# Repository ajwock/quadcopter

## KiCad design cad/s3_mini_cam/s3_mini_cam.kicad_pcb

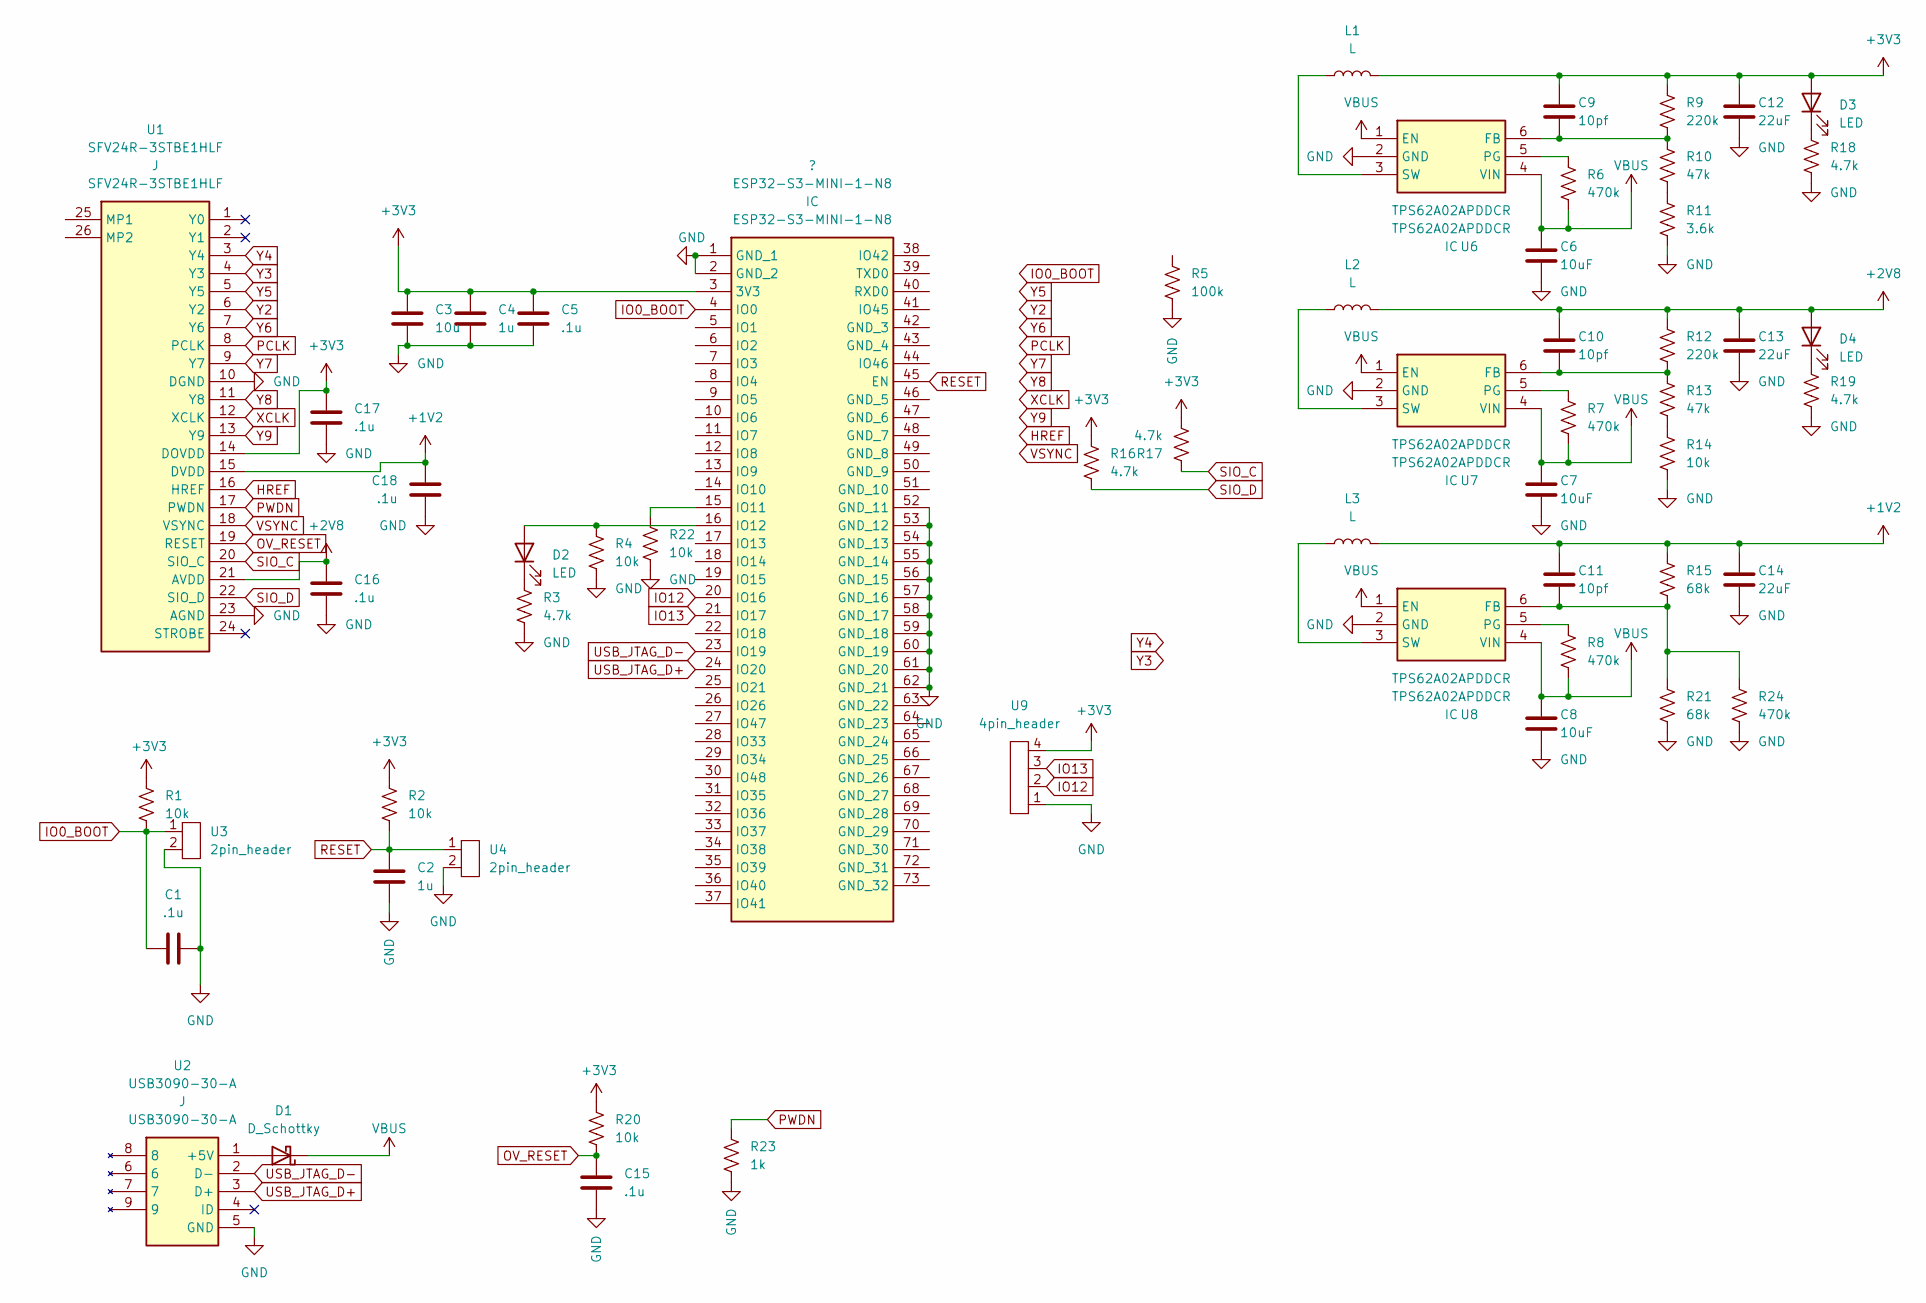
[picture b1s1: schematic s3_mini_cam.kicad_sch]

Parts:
C1, C5, C15, C16, C17, C18: .1u; C_0603_1608Metric
C2, C4: 1u; C_0603_1608Metric
C3: 10u; C_0603_1608Metric
C6, C7, C8: 10uF; 0603_cap
C9, C10, C11: 10pf; 0603_cap
C12, C13, C14: 22uF; 0603_cap
D1: D_Schottky; SM6F22AY
D2, D3, D4: LED; LED_0603_1608Metric
L1, L2, L3: L; L_0603_1608Metric
R1, R2, R20: 10k; R_0603_1608Metric
R3, R16, R17, R18, R19: 4.7k; 0603_resistor
R4, R14, R22: 10k; 0603_resistor
R5: 100k; 0603_resistor
R6, R7, R8, R24: 470k; 0603_resistor
R9, R12: 220k; 0603_resistor
R10, R13: 47k; 0603_resistor
R11: 3.6k; 0603_resistor
R15, R21: 68k; 0603_resistor
R23: 1k; R_0603_1608Metric
U1: SFV24R-3STBE1HLF; SFV24R3STBE1HLF; Mouser Part Number 649-SFV24R-3STBE1HLF
U2: USB3090-30-A; USB309030A; Mouser Part Number 640-USB3090-30-A
U3, U4: 2pin_header; 2-bb
U6, U7, U8: TPS62A02APDDCR; SOT95P280X110-6N; Mouser Part Number 595-TPS62A02APDDCR
U9: 4pin_header; 4-bb

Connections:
+1V2: C11.1, C14.1, C18.1, L3.2, R15.1, U1.15 (DVDD)
+2V8: C10.1, C13.1, C16.1, D4.2 (A), L2.2, R12.1, U1.21 (AVDD)
+3V3: C3.1, C4.1, C5.1, C9.1, C12.1, C17.1, D3.2 (A), L1.2, R1.1, R2.1, R9.1, R16.1, R17.2, R20.1, U1.14 (DOVDD), U9.4; also elsewhere on the board
GND: C1.1, C2.2, C3.2, C4.2, C5.2, C6.2, C7.2, C8.2, C12.2, C13.2, C14.2, C15.2, C16.2, C17.2, C18.2, R3.2, R4.2, R5.2, R11.2, R14.2, R18.2, R19.2, R21.2, R22.2, R23.2, R24.2, U1.10 (DGND), U1.23 (AGND), U2.5 (GND), U3.2, U4.2, U6.2 (GND), U7.2 (GND), U8.2 (GND), U9.1; also elsewhere on the board
HREF: U1.16 (HREF); also elsewhere on the board
IO0_BOOT: C1.2, R1.2, U3.1; also elsewhere on the board
IO12: U9.2; also elsewhere on the board
IO13: U9.3; also elsewhere on the board
unnamed: C9.2, R9.2, R10.1, U6.6 (FB)
unnamed: C10.2, R12.2, R13.1, U7.6 (FB)
unnamed: C11.2, R15.2, R21.1, R24.1, U8.6 (FB)
unnamed: D1.2 (A), U2.1 (+5V)
unnamed: D2.1 (K), R3.1
unnamed 13: D2.2 (A), R4.1; also elsewhere on the board
unnamed: D3.1 (K), R18.1
unnamed: D4.1 (K), R19.1
unnamed: L1.1, U6.3 (SW)
unnamed: L2.1, U7.3 (SW)
unnamed: L3.1, U8.3 (SW)
unnamed: R6.1, U6.5 (PG)
unnamed: R7.1, U7.5 (PG)
unnamed: R8.1, U8.5 (PG)
unnamed: R10.2, R11.1
unnamed: R13.2, R14.1
unnamed 24: R22.1; also elsewhere on the board
unnamed 25: R5.1; also elsewhere on the board
OV_RESET: C15.1, R20.2, U1.19 (RESET)
PCLK: U1.8 (PCLK); also elsewhere on the board
PWDN: R23.1, U1.17 (PWDN)
RESET: C2.1, R2.2, U4.1; also elsewhere on the board
SIO_C: R17.1, U1.20 (SIO_C); also elsewhere on the board
SIO_D: R16.2, U1.22 (SIO_D); also elsewhere on the board
USB_JTAG_D+: U2.3 (D+); also elsewhere on the board
USB_JTAG_D-: U2.2 (D-); also elsewhere on the board
VBUS: C6.1, C7.1, C8.1, D1.1 (K), R6.2, R7.2, R8.2, U6.1 (EN), U6.4 (VIN), U7.1 (EN), U7.4 (VIN), U8.1 (EN), U8.4 (VIN)
VSYNC: U1.18 (VSYNC); also elsewhere on the board
XCLK: U1.12 (XCLK); also elsewhere on the board
Y2: U1.6 (Y2); also elsewhere on the board
Y3: U1.4 (Y3); also elsewhere on the board
Y4: U1.3 (Y4); also elsewhere on the board
Y5: U1.5 (Y5); also elsewhere on the board
Y6: U1.7 (Y6); also elsewhere on the board
Y7: U1.9 (Y7); also elsewhere on the board
Y8: U1.11 (Y8); also elsewhere on the board
Y9: U1.13 (Y9); also elsewhere on the board

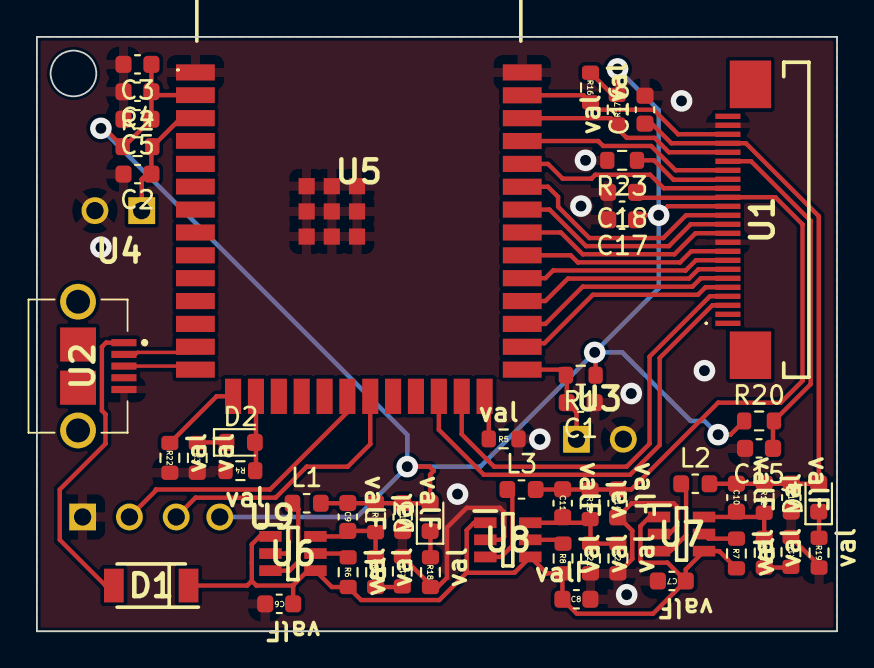
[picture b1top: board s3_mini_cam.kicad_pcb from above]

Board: 2 copper layers, 44.4 x 33.0 mm, 58 parts (0 on the bottom side), 45 nets.

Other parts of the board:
U5: ESP32-S3-WROOM-1-N8R2; ESP32S3WROOM1N8R2

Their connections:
+3V3: U5.2 (3V3); also elsewhere on the board
GND: U5.1 (GND_1), U5.40 (GND_2), U5.41 (GND_3), U5.42 (GND_4), U5.43 (GND_5), U5.44 (GND_6), U5.45 (GND_7), U5.46 (GND_8), U5.47 (GND_9), U5.48 (GND_10), U5.49 (GND_11); also elsewhere on the board
HREF: U5.36 (RXD0); also elsewhere on the board
IO0_BOOT: U5.27 (IO0); also elsewhere on the board
IO12: U5.20 (IO12); also elsewhere on the board
IO13: U5.21 (IO13); also elsewhere on the board
unnamed 13: U5.16 (IO46); also elsewhere on the board
unnamed 24: U5.15 (IO3); also elsewhere on the board
unnamed 25: U5.26 (IO45); also elsewhere on the board
PCLK: U5.31 (IO38); also elsewhere on the board
RESET: U5.3 (EN); also elsewhere on the board
SIO_C: U5.38 (IO2); also elsewhere on the board
SIO_D: U5.39 (IO1); also elsewhere on the board
USB_JTAG_D+: U5.14 (IO20); also elsewhere on the board
USB_JTAG_D-: U5.13 (IO19); also elsewhere on the board
VSYNC: U5.37 (TXD0); also elsewhere on the board
XCLK: U5.34 (IO41); also elsewhere on the board
Y2: U5.29 (IO36); also elsewhere on the board
Y3: U5.25 (IO48); also elsewhere on the board
Y4: U5.24 (IO47); also elsewhere on the board
Y5: U5.28 (IO35); also elsewhere on the board
Y6: U5.30 (IO37); also elsewhere on the board
Y7: U5.32 (IO39); also elsewhere on the board
Y8: U5.33 (IO40); also elsewhere on the board
Y9: U5.35 (IO42); also elsewhere on the board

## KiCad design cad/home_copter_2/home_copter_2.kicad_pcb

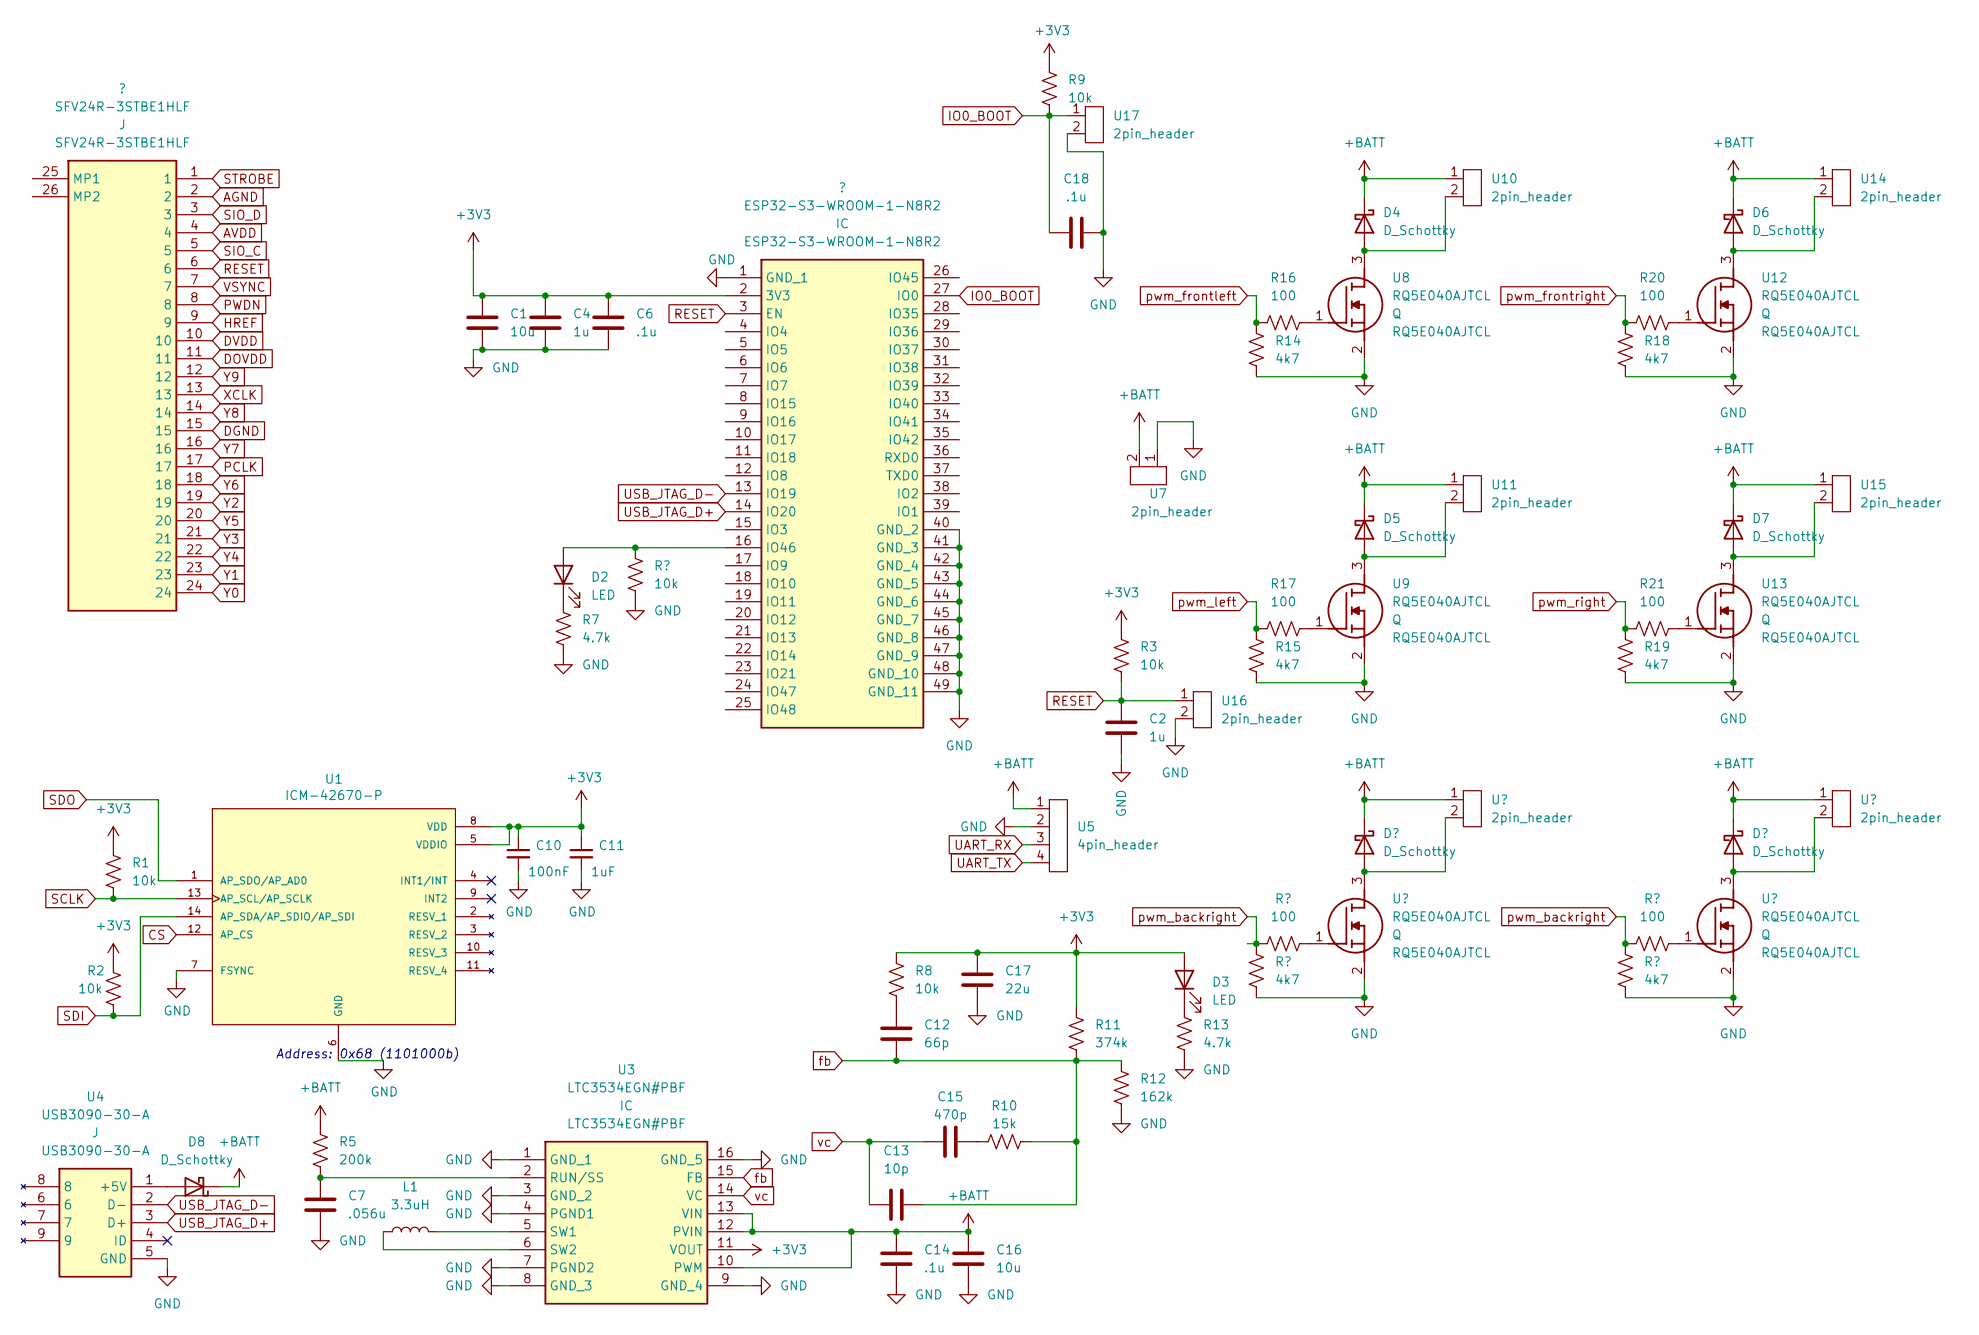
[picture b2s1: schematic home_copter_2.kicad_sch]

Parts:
C1, C16: 10u; C_0603_1608Metric
C2, C4: 1u; C_0603_1608Metric
C6, C18: .1u; C_0603_1608Metric
C7: .056u; C_0603_1608Metric
C10: 100nF; C_0603_1608Metric; LCSC C15195
C11: 1uF; C_0603_1608Metric; LCSC C1525
C12: 66p; C_0603_1608Metric
C13: 10p; C_0603_1608Metric
C14: .1u; C_0603_1608Metric_Pad1.08x0.95mm_HandSolder
C15: 470p; C_0603_1608Metric
C17: 22u; C_0603_1608Metric
D2, D3: LED; LED_0603_1608Metric
D4, D5, D6, D7, D8: D_Schottky; SM6F22AY
L1: 3.3uH; L_0603_1608Metric
R1, R2, R3, R8, R9: 10k; R_0603_1608Metric
R5: 200k; R_0603_1608Metric
R7, R13: 4.7k; 0603_resistor
R10: 15k; R_0603_1608Metric
R11: 374k; C_0603_1608Metric
R12: 162k; R_0603_1608Metric
R14, R15, R18, R19: 4k7; R_0603_1608Metric
R16, R17, R20, R21: 100; R_0603_1608Metric
U1: ICM-42670-P; ICM-42670-hand-solder; PARTREV 1.0
U3: LTC3534EGN#PBF; SOP64P601X175-16N; Mouser Part Number 584-LTC3534EGN#PBF
U4: USB3090-30-A; USB309030A; Mouser Part Number 640-USB3090-30-A
U5: 4pin_header; 4-bb
U7, U10, U11, U14, U15, U16, U17: 2pin_header; 2-bb
U8, U9, U12, U13: RQ5E040AJTCL; SOT95P280X100-3N; Mouser Part Number 755-RQ5E040AJTCL

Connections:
+3V3: C1.1, C4.1, C6.1, C10.1, C11.1, C17.1, D3.2 (A), R1.1, R2.1, R3.1, R8.1, R9.1, R11.1, U1.5 (VDDIO), U1.8 (VDD), U3.11 (VOUT); also elsewhere on the board
CS: U1.12 (AP_CS); also elsewhere on the board
GND: C1.2, C2.2, C4.2, C6.2, C7.2, C10.2, C11.2, C14.1, C16.2, C17.2, C18.1, R7.2, R12.2, R13.2, R14.2, R15.2, R18.2, R19.2, U1.6 (GND), U1.7 (FSYNC), U3.1 (GND_1), U3.3 (GND_2), U3.4 (PGND1), U3.7 (PGND2), U3.8 (GND_3), U3.9 (GND_4), U3.16 (GND_5), U4.5 (GND), U5.2, U7.1, U8.2 (S), U9.2 (S), U12.2 (S), U13.2 (S), U16.2, U17.2; also elsewhere on the board
IO9_BOOT: C18.2, R9.2, U17.1; also elsewhere on the board
IO18_USB_D+: U4.3 (D+); also elsewhere on the board
IO18_USB_D-: U4.2 (D-); also elsewhere on the board
unnamed: C7.1, R5.2, U3.2 (RUN/SS)
unnamed: C12.1, R8.2
unnamed: C15.2, R10.1
unnamed: D2.1 (K), R7.1
unnamed 12: D2.2 (A); also elsewhere on the board
unnamed: D3.1 (K), R13.1
unnamed: D4.2 (A), U8.3 (D), U10.2
unnamed: D5.2 (A), U9.3 (D), U11.2
unnamed: D6.2 (A), U12.3 (D), U14.2
unnamed: D7.2 (A), U13.3 (D), U15.2
unnamed: L1.1, U3.6 (SW2)
unnamed: L1.2, U3.5 (SW1)
unnamed: R16.2, U8.1 (G)
unnamed: R17.2, U9.1 (G)
unnamed: R20.2, U12.1 (G)
unnamed: R21.2, U13.1 (G)
unnamed: D8.2 (A), U4.1 (+5V)
RESET: C2.1, R3.2, U16.1; also elsewhere on the board
SCLK: R1.2, U1.13 (AP_SCL/AP_SCLK); also elsewhere on the board
SDI: R2.2, U1.14 (AP_SDA/AP_SDIO/AP_SDI); also elsewhere on the board
SDO: U1.1 (AP_SDO/AP_AD0); also elsewhere on the board
UART_RX: U5.3; also elsewhere on the board
UART_TX: U5.4; also elsewhere on the board
fb: C12.2, C13.2, R10.2, R11.2, R12.1, U3.15 (FB)
pwm_backleft: R15.1, R17.1; also elsewhere on the board
pwm_backright: R19.1, R21.1; also elsewhere on the board
pwm_frontleft: R14.1, R16.1; also elsewhere on the board
pwm_frontright: R18.1, R20.1; also elsewhere on the board
vc: C13.1, C15.1, U3.14 (VC)

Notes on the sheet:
Address: 0x68 (1101000b)

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
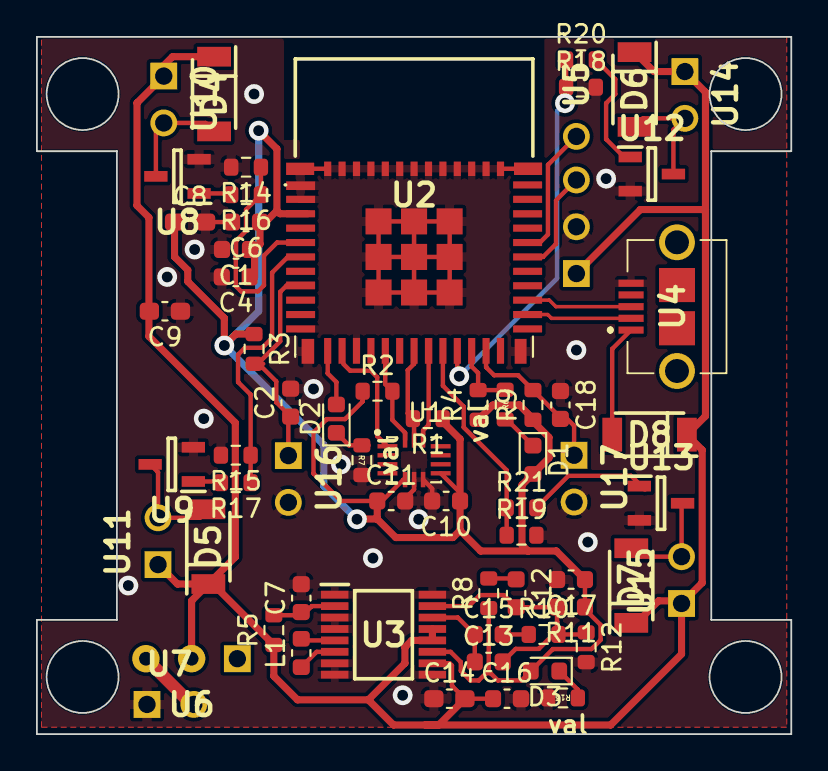
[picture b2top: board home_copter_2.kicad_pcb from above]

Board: 2 copper layers, 41.9 x 38.7 mm, 63 parts (0 on the bottom side), 39 nets.

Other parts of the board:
C8, C9: .1u; C_0603_1608Metric_Pad1.08x0.95mm_HandSolder
D1: LED; LED_0603_1608Metric
R4: 10k; R_0603_1608Metric
R6: 4.7k; 0603_resistor
U2: ESP32-C3-MINI-1-H4X; ESP32C3MINI1H4X_hand_solder
U6: 3pin_header; 3-bb

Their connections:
+3V3: C8.1, D1.2 (A), R4.1, U2.3 (3V3); also elsewhere on the board
CS: U2.19 (IO5); also elsewhere on the board
GND: C8.2, C9.1, U2.1 (GND_1), U2.2 (GND_2), U2.11 (GND_3), U2.14 (GND_4), U2.36 (GND_5), U2.37 (GND_6), U2.38 (GND_7), U2.39 (GND_8), U2.40 (GND_9), U2.41 (GND_10), U2.42 (GND_11), U2.43 (GND_12), U2.44 (GND_13), U2.45 (GND_14), U2.46 (GND_15), U2.47 (GND_16), U2.48 (GND_17), U2.49 (GND_18), U2.50 (GND_19), U2.51 (GND_20), U2.52 (GND_21), U2.53 (GND_22), U2.54 (GND_23), U2.55 (GND_24), U2.56 (GND_25), U2.57 (GND_26), U2.58 (GND_27), U2.59 (GND_28), U2.60 (GND_29), U2.61 (GND_30); also elsewhere on the board
IO8: R4.2, R6.2, U2.22 (IO8)
IO9_BOOT: U2.23 (IO9); also elsewhere on the board
IO18_USB_D+: U2.27 (IO19); also elsewhere on the board
IO18_USB_D-: U2.26 (IO18); also elsewhere on the board
unnamed: D1.1 (K), R6.1
unnamed 12: U2.12 (IO0); also elsewhere on the board
RESET: U2.8 (EN); also elsewhere on the board
SCLK: U2.18 (IO4); also elsewhere on the board
SDI: U2.16 (IO10); also elsewhere on the board
SDO: U2.13 (IO1); also elsewhere on the board
UART_RX: U2.30 (RXD0); also elsewhere on the board
UART_TX: U2.31 (TXD0); also elsewhere on the board
pwm_backleft: U2.6 (IO3); also elsewhere on the board
pwm_backright: U2.20 (IO6); also elsewhere on the board
pwm_frontleft: U2.5 (IO2); also elsewhere on the board
pwm_frontright: U2.21 (IO7); also elsewhere on the board

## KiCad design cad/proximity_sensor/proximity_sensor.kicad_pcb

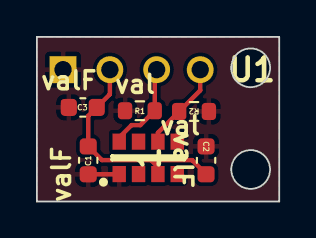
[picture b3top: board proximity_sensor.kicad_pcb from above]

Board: 2 copper layers, 13.5 x 9.1 mm, 7 parts (0 on the bottom side), 4 nets.

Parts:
1: VCNL3040; SON108P200X400X115-8N
C1: 0.1uF; 0603_cap
C2: 1uF; 0603_cap
C3: 22uF; 0603_cap
R1, R2: 2.2k; 0603_resistor
U1: 4pin_header; 4-bb

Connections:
+3.3V: 1.1 (VDD), 1.5 (A), C1.1, C2.1, C3.1, R1.1, R2.1, U1.1
GND: 1.3 (GND), C1.2, C2.2, C3.2, U1.2
unnamed: 1.6 (SCLK), R2.2, U1.4
unnamed: 1.8 (SDAT), R1.2, U1.3

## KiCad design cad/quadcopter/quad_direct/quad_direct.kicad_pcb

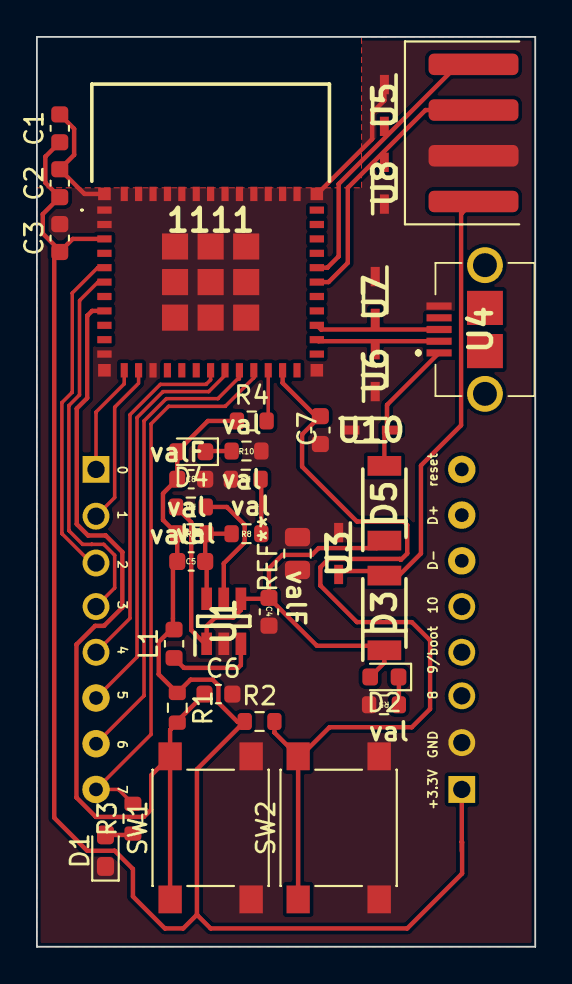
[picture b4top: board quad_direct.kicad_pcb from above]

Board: 2 copper layers, 27.7 x 50.5 mm, 37 parts (0 on the bottom side), 27 nets.

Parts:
1111: ESP32-C3-MINI-1-H4X; ESP32C3MINI1H4X
C1: 10u; C_0603_1608Metric
C2, C6: 1u; C_0603_1608Metric
C3, C7: .1u; C_0603_1608Metric
C4: 10uF; 0603_cap
C5: 10pf; 0603_cap
C8: 22uF; 0603_cap
D1: LED; LED_0603_1608Metric_Pad1.05x0.95mm_HandSolder
D2, D4: LED; LED_0603_1608Metric
D3, D5: D_Schottky; SM6F22AY
L1: L; L_0603_1608Metric
R1, R2, R3, R4: 10k; R_0603_1608Metric
R5: 6.8k; 0603_resistor
R6: 470k; 0603_resistor
R7: 220k; 0603_resistor
R8: 47k; 0603_resistor
R9: 2.2k; 0603_resistor
R10: 4.7k; 0603_resistor
SW1, SW2: SW_Push; SW_Push_1P1T_NO_6x6mm_H9.5mm
U1: TPS62A02APDDCR; SOT95P280X110-6N
U2: esp32c3_boardout
U3, U5, U6, U7, U8, U10: SD03C-7; SOD2513X120N
U4: USB3090-30-A; USB309030A
U9: 4pin_header; 4-rightangle-smt

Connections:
+3.3V: 1111.3 (3V3), C1.1, C2.1, C3.1, C5.1, C8.1, D4.2 (A), L1.2, R1.1, R2.1, R4.1, R7.1, U2.16 (+3V3)
GND: 1111.1 (GND_1), 1111.2 (GND_2), 1111.11 (GND_3), 1111.14 (GND_4), 1111.36 (GND_5), 1111.37 (GND_6), 1111.38 (GND_7), 1111.39 (GND_8), 1111.40 (GND_9), 1111.41 (GND_10), 1111.42 (GND_11), 1111.43 (GND_12), 1111.44 (GND_13), 1111.45 (GND_14), 1111.46 (GND_15), 1111.47 (GND_16), 1111.48 (GND_17), 1111.49 (GND_18), 1111.50 (GND_19), 1111.51 (GND_20), 1111.52 (GND_21), 1111.53 (GND_22), 1111.54 (GND_23), 1111.55 (GND_24), 1111.56 (GND_25), 1111.57 (GND_26), 1111.58 (GND_27), 1111.59 (GND_28), 1111.60 (GND_29), 1111.61 (GND_30), C1.2, C2.2, C3.2, C4.2, C6.2, C7.1, C8.2, D1.1 (K), R5.2, R9.2, R10.2, SW1.2, SW2.2, U1.2 (GND), U2.15 (gnd), U3.1, U4.5 (GND), U5.1, U6.1, U7.1, U8.1, U9.2, U10.1
IO0: 1111.12 (IO0), U2.1 (io0)
IO1: 1111.13 (IO1), U2.2 (io1)
IO2: 1111.5 (IO2), U2.3 (io2)
IO3: 1111.6 (IO3), U2.4 (io3)
IO4: 1111.18 (IO4), U2.5 (io4)
IO5: 1111.19 (IO5), U2.6 (io5)
IO6: 1111.20 (IO6), U2.7 (io6)
IO7: 1111.21 (IO7), R3.2, U2.8 (io7)
IO8: 1111.22 (IO8), R4.2
IO9_BOOT: 1111.23 (IO9), C7.2, R2.2, SW2.1
IO18_USB_D-: 1111.26 (IO18), U4.2 (D-), U6.2
IO19_USB_D+: 1111.27 (IO19), U4.3 (D+), U7.2
unnamed: C5.2, R7.2, R8.1, U1.6 (FB)
unnamed: D1.2 (A), R3.1
unnamed: D2.1 (K), R5.1
unnamed: D3.2 (A), U3.2, U9.1
unnamed: D4.1 (K), R10.1
unnamed: D5.2 (A), U4.1 (+5V), U10.2
unnamed: L1.1, U1.3 (SW)
unnamed: R6.1, U1.5 (PG)
unnamed: R8.2, R9.1
RESET: 1111.8 (EN), C6.1, R1.2, SW1.1
UART_RX: 1111.30 (RXD0), U8.2, U9.3
UART_TX: 1111.31 (TXD0), U5.2, U9.4
VBUS: C4.1, D2.2 (A), D3.1 (K), D5.1 (K), R6.2, U1.1 (EN), U1.4 (VIN)

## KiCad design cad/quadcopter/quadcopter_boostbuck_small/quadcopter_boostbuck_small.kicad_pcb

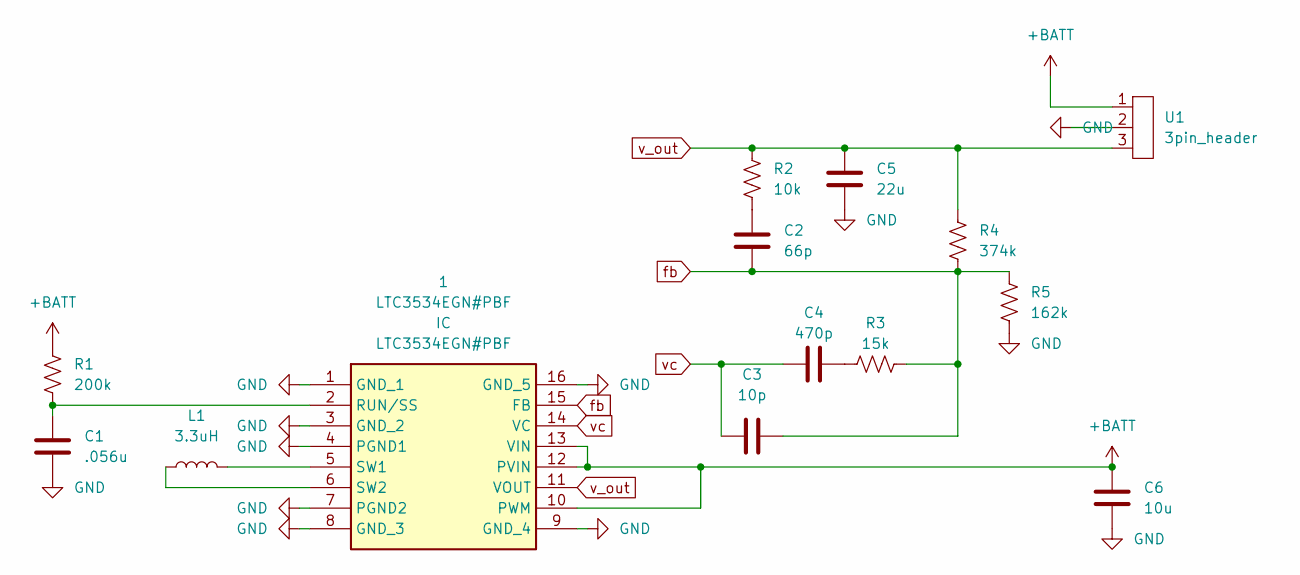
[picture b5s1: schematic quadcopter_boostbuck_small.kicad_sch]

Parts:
1: LTC3534EGN#PBF; SOP64P601X175-16N; Mouser Part Number 584-LTC3534EGN#PBF
C1: .056u; C_0603_1608Metric
C2: 66p; C_0603_1608Metric
C3: 10p; C_0603_1608Metric
C4: 470p; C_0603_1608Metric
C5: 22u; C_0603_1608Metric
C6: 10u; C_0603_1608Metric
L1: 3.3uH; L_0603_1608Metric
R1: 200k; R_0603_1608Metric
R2: 10k; R_0603_1608Metric
R3: 15k; R_0603_1608Metric
R4: 374k; C_0603_1608Metric
R5: 162k; R_0603_1608Metric
U1: 3pin_header; 3-bb

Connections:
+BATT: 1.10 (PWM), 1.12 (PVIN), 1.13 (VIN), C6.1, R1.1, U1.1
GND: 1.1 (GND_1), 1.3 (GND_2), 1.4 (PGND1), 1.7 (PGND2), 1.8 (GND_3), 1.9 (GND_4), 1.16 (GND_5), C1.2, C5.2, C6.2, R5.2, U1.2
unnamed: 1.2 (RUN/SS), C1.1, R1.2
unnamed: 1.5 (SW1), L1.2
unnamed: 1.6 (SW2), L1.1
unnamed: C2.1, R2.2
unnamed: C4.2, R3.1
fb: 1.15 (FB), C2.2, C3.2, R3.2, R4.2, R5.1
v_out: 1.11 (VOUT), C5.1, R2.1, R4.1, U1.3
vc: 1.14 (VC), C3.1, C4.1

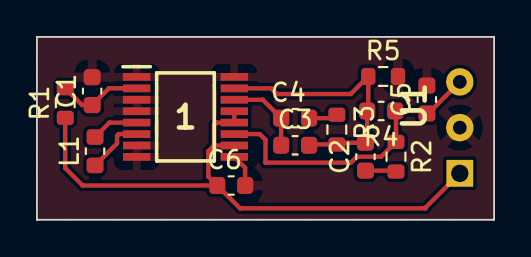
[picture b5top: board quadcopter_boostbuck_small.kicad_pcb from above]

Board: 2 copper layers, 25.4 x 10.2 mm, 14 parts (0 on the bottom side), 10 nets.

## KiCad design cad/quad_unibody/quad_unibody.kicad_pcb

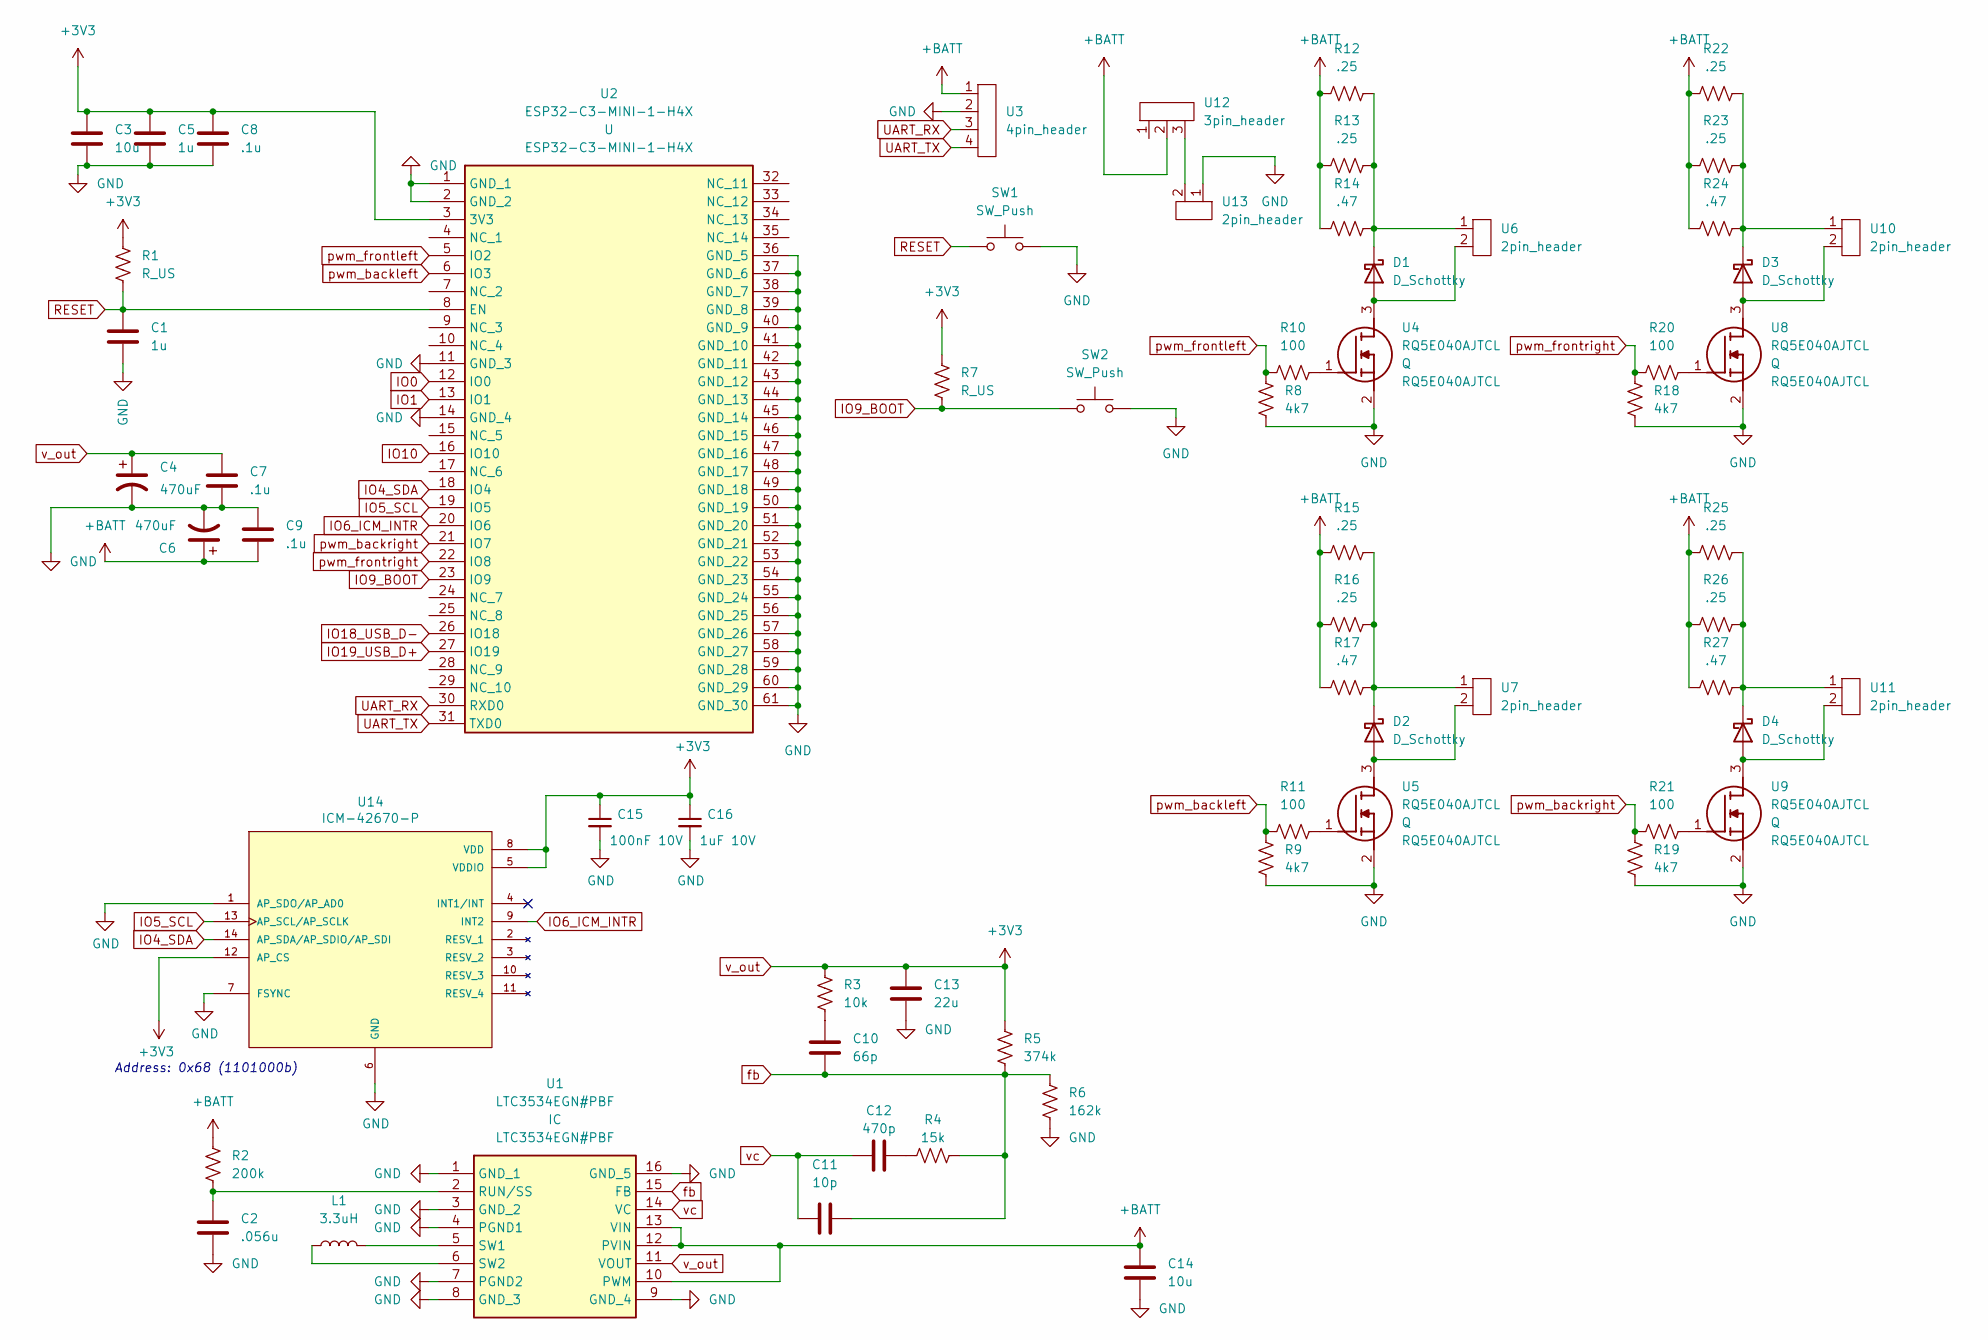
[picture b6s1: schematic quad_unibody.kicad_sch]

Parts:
C1, C5: 1u; C_0603_1608Metric
C2: .056u; C_0603_1608Metric
C3, C14: 10u; C_0603_1608Metric
C4, C6: 470uF; CP_Radial_D6.3mm_P2.50mm
C7, C9: .1u; C_0603_1608Metric_Pad1.08x0.95mm_HandSolder
C8: .1u; C_0603_1608Metric
C10: 66p; C_0603_1608Metric
C11: 10p; C_0603_1608Metric
C12: 470p; C_0603_1608Metric
C13: 22u; C_0603_1608Metric
C15: 100nF 10V; C_0603_1608Metric; LCSC C15195
C16: 1uF 10V; C_0603_1608Metric; LCSC C1525
D1, D2, D3, D4: D_Schottky; SM6F22AY
L1: 3.3uH; L_0603_1608Metric
R1, R7: R_US; R_0603_1608Metric
R2: 200k; R_0603_1608Metric
R3: 10k; R_0603_1608Metric
R4: 15k; R_0603_1608Metric
R5: 374k; C_0603_1608Metric
R6: 162k; R_0603_1608Metric
R8, R9, R18, R19: 4k7; R_0603_1608Metric
R10, R11, R20, R21: 100; R_0603_1608Metric
R12, R13, R15, R16, R22, R23, R25, R26: .25; R_0805_2012Metric
R14, R17, R24, R27: .47; R_Axial_DIN0309_L9.0mm_D3.2mm_P12.70mm_Horizontal
SW1, SW2: SW_Push; SW_PUSH_6mm
U1: LTC3534EGN#PBF; SOP64P601X175-16N; Mouser Part Number 584-LTC3534EGN#PBF
U2: ESP32-C3-MINI-1-H4X; ESP32C3MINI1H4X; Mouser Part Number 356-ESP32C3MINI1H4X
U3: 4pin_header; 4-bb
U4, U5, U8, U9: RQ5E040AJTCL; SOT95P280X100-3N; Mouser Part Number 755-RQ5E040AJTCL
U6, U7, U10, U11, U13: 2pin_header; 2-bb
U12: 3pin_header; 3-bb
U14: ICM-42670-P; IC_ICM-42670-P; PARTREV 1.0

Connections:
+BATT: C6.1, C9.2, C14.1, R2.1, R12.1, R13.1, R14.1, R15.1, R16.1, R17.1, R22.1, R23.1, R24.1, R25.1, R26.1, R27.1, U1.10 (PWM), U1.12 (PVIN), U1.13 (VIN), U3.1, U12.2
GND: C1.2, C2.2, C3.2, C4.2, C5.2, C6.2, C7.2, C8.2, C9.1, C13.2, C14.2, C15.2, C16.2, R6.2, R8.2, R9.2, R18.2, R19.2, SW1.2, SW2.2, U1.1 (GND_1), U1.3 (GND_2), U1.4 (PGND1), U1.7 (PGND2), U1.8 (GND_3), U1.9 (GND_4), U1.16 (GND_5), U2.1 (GND_1), U2.2 (GND_2), U2.11 (GND_3), U2.14 (GND_4), U2.36 (GND_5), U2.37 (GND_6), U2.38 (GND_7), U2.39 (GND_8), U2.40 (GND_9), U2.41 (GND_10), U2.42 (GND_11), U2.43 (GND_12), U2.44 (GND_13), U2.45 (GND_14), U2.46 (GND_15), U2.47 (GND_16), U2.48 (GND_17), U2.49 (GND_18), U2.50 (GND_19), U2.51 (GND_20), U2.52 (GND_21), U2.53 (GND_22), U2.54 (GND_23), U2.55 (GND_24), U2.56 (GND_25), U2.57 (GND_26), U2.58 (GND_27), U2.59 (GND_28), U2.60 (GND_29), U2.61 (GND_30), U3.2, U4.2 (S), U5.2 (S), U8.2 (S), U9.2 (S), U13.1, U14.1 (AP_SDO/AP_AD0), U14.6 (GND), U14.7 (FSYNC)
IO0: U2.12 (IO0)
IO1: U2.13 (IO1)
IO4_SDA: U2.18 (IO4), U14.14 (AP_SDA/AP_SDIO/AP_SDI); also elsewhere on the board
IO5_SCL: U2.19 (IO5), U14.13 (AP_SCL/AP_SCLK); also elsewhere on the board
IO6_ICM_INTR: U2.20 (IO6), U14.9 (INT2)
IO9_BOOT: R7.2, SW2.1, U2.23 (IO9)
IO10: U2.16 (IO10)
IO18_USB_D-: U2.26 (IO18)
unnamed: C2.1, R2.2, U1.2 (RUN/SS)
unnamed: C10.1, R3.2
unnamed: C12.2, R4.1
unnamed: D1.1 (K), R12.2, R13.2, R14.2, U6.1
unnamed: D1.2 (A), U4.3 (D), U6.2
unnamed: D2.1 (K), R15.2, R16.2, R17.2, U7.1
unnamed: D2.2 (A), U5.3 (D), U7.2
unnamed: D3.1 (K), R22.2, R23.2, R24.2, U10.1
unnamed: D3.2 (A), U8.3 (D), U10.2
unnamed: D4.1 (K), R25.2, R26.2, R27.2, U11.1
unnamed: D4.2 (A), U9.3 (D), U11.2
unnamed: L1.1, U1.6 (SW2)
unnamed: L1.2, U1.5 (SW1)
unnamed: R10.2, U4.1 (G)
unnamed: R11.2, U5.1 (G)
unnamed: R20.2, U8.1 (G)
unnamed: R21.2, U9.1 (G)
unnamed: U12.3, U13.2
RESET: C1.1, R1.2, SW1.1, U2.8 (EN)
UART_RX: U2.30 (RXD0), U3.3
UART_TX: U2.31 (TXD0), U3.4
fb: C10.2, C11.2, R4.2, R5.2, R6.1, U1.15 (FB)
pwm_backleft: R9.1, R11.1, U2.6 (IO3)
pwm_backright: R19.1, R21.1, U2.21 (IO7)
pwm_frontleft: R8.1, R10.1, U2.5 (IO2)
v_out: C3.1, C4.1, C5.1, C7.1, C8.1, C13.1, C15.1, C16.1, R1.1, R3.1, R5.1, R7.1, U1.11 (VOUT), U2.3 (3V3), U14.5 (VDDIO), U14.8 (VDD), U14.12 (AP_CS); also elsewhere on the board
vc: C11.1, C12.1, U1.14 (VC)

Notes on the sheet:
Address: 0x68 (1101000b)

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
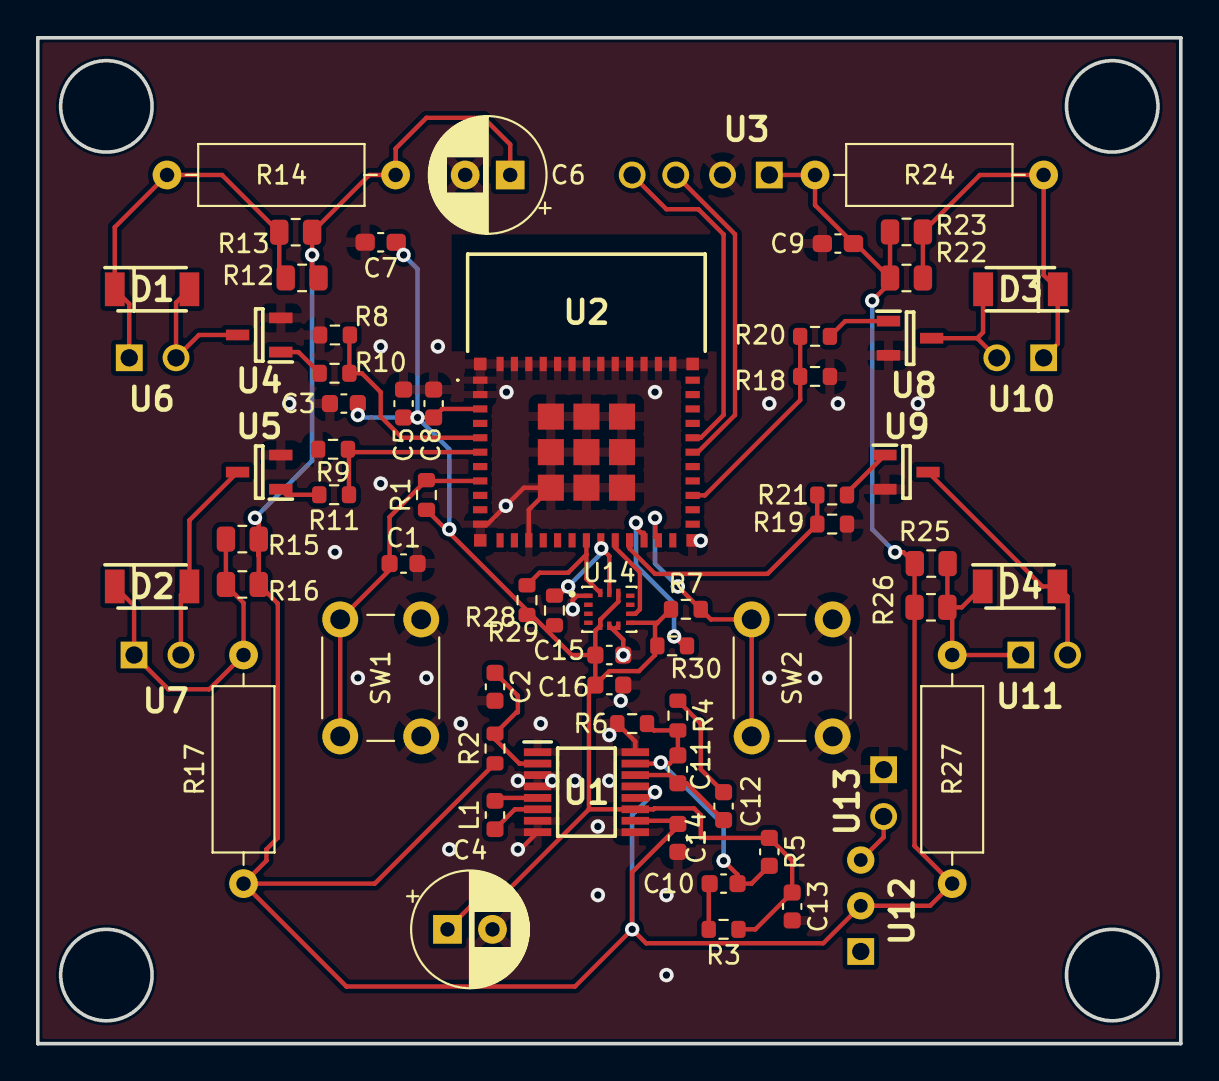
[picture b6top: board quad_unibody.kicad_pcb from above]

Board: 2 copper layers, 63.5 x 55.9 mm, 67 parts (0 on the bottom side), 35 nets.

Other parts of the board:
R28, R29, R30: 10k; R_0603_1608Metric

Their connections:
IO4_SDA: R28.2; also elsewhere on the board
IO5_SCL: R29.2; also elsewhere on the board
v_out: R28.1, R29.1, R30.1; also elsewhere on the board
